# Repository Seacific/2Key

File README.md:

# 2Key
Simple 2 Key keypad designed for the rhythm game osu!

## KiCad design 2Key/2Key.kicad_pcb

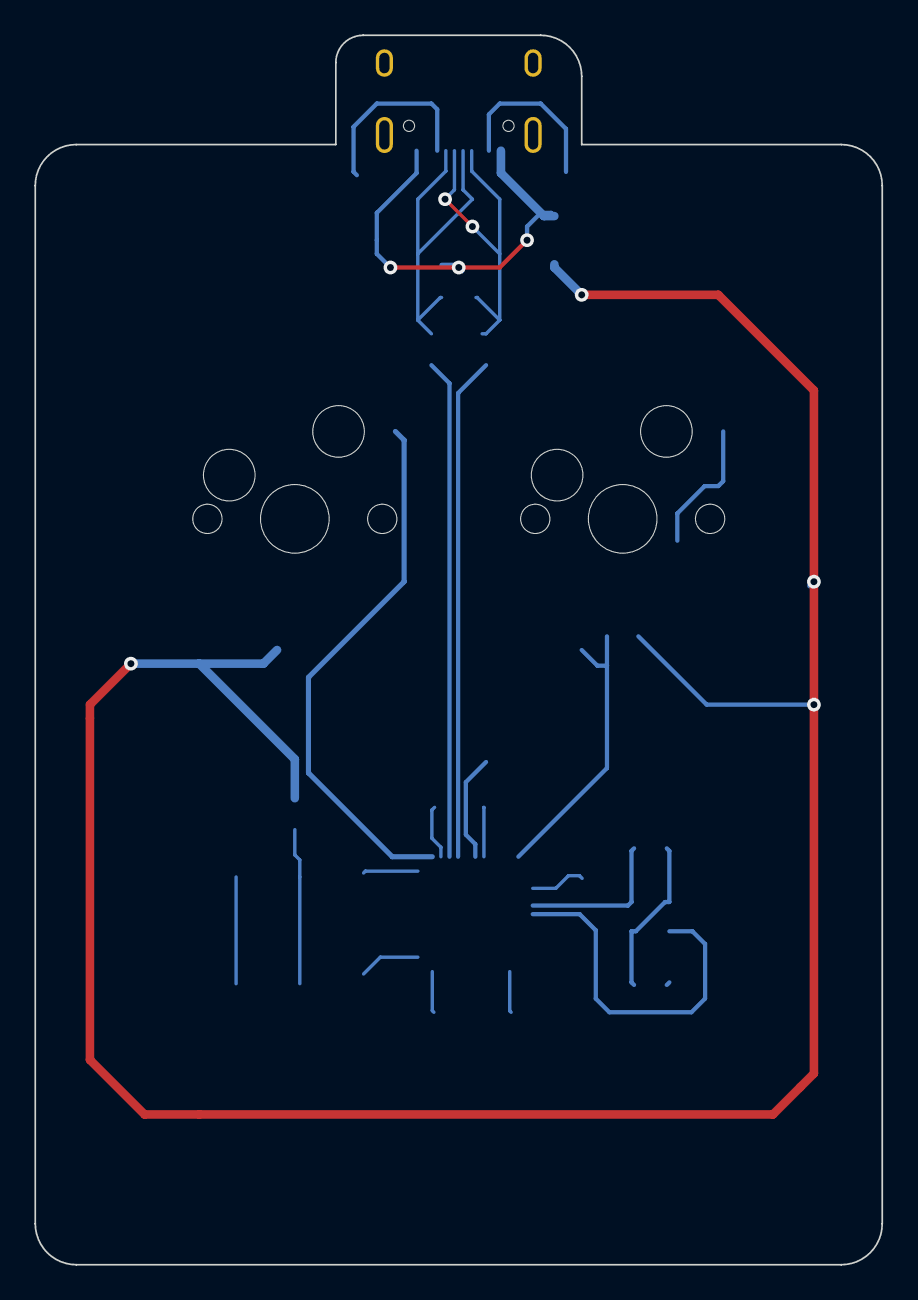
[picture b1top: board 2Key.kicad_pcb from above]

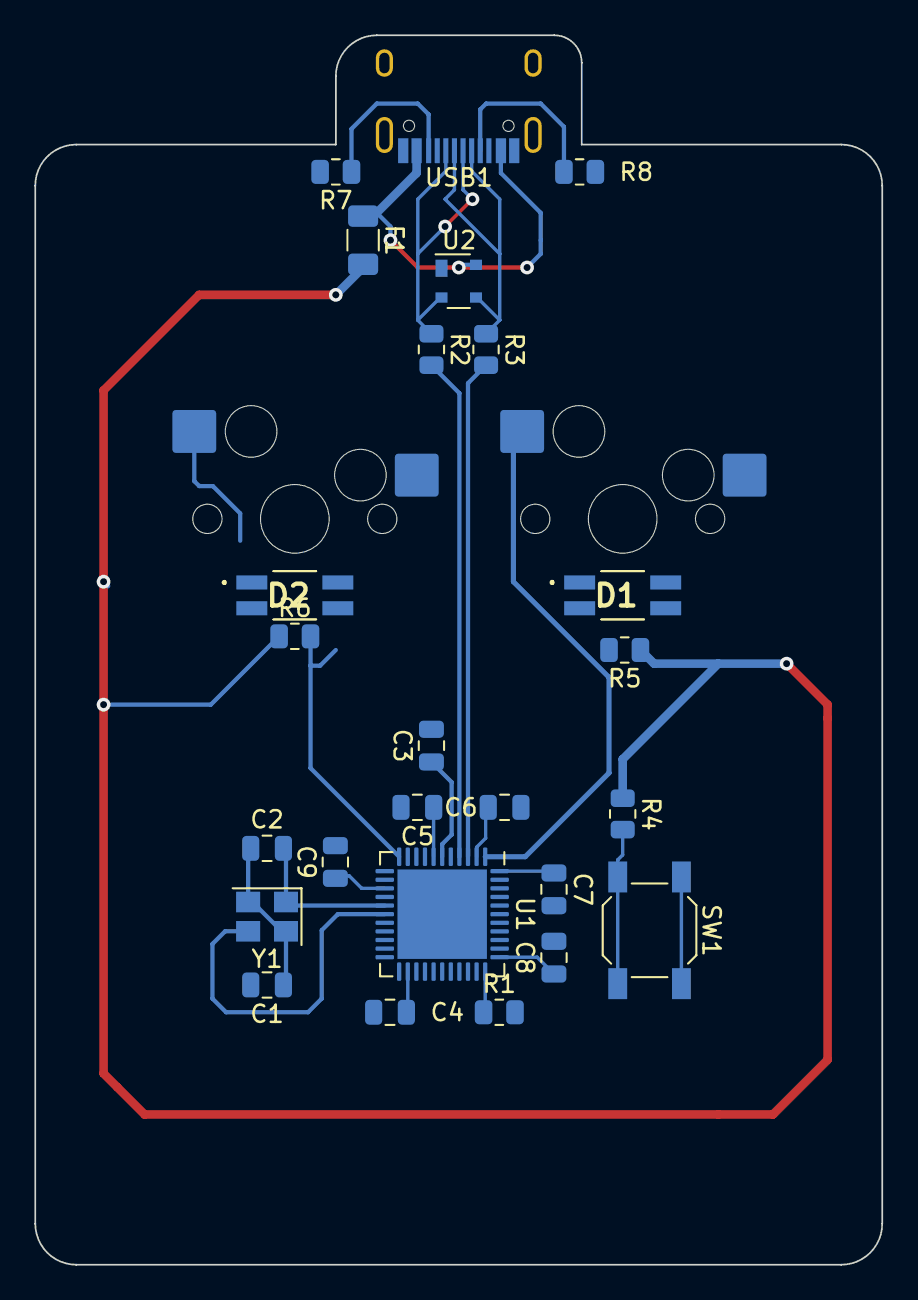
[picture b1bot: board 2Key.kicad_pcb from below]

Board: 2 copper layers, 49.2 x 71.4 mm, 27 parts (25 on the bottom side), 18 nets.

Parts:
C1, C2: 22pF; C_0805_2012Metric
C3: 1uF; C_0805_2012Metric
C4, C5, C6, C8, C9: 0.1uF; C_0805_2012Metric
C7: 10uF; C_0805_2012Metric
D1, D2: SK6812MINI; SK6812MINIE
F1: 500mA; Fuse_1206_3216Metric
MX1, MX2: MX-NoLED; MX-Hotswap-1U
R1, R4, R5, R6: 10k; R_0805_2012Metric
R2, R3: 22; R_0805_2012Metric
R7, R8: 5.1k; R_0805_2012Metric
SW1: SW_Push; SW_SPST_SKQG_WithStem
U1: ATmega32U4-M; QFN-44-1EP_7x7mm_P0.5mm_EP5.2x5.2mm
U2: PRTR5V0U2X; SOT-143
USB1: HRO-TYPE-C-31-M-12; HRO-TYPE-C-31-M-12-Assembly
Y1: 16MHz; Crystal_SMD_3225-4Pin_3.2x2.5mm

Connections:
+5V: C4.1, C5.1, C6.1, C7.1, C8.1, C9.1, D1.4 (VDD), D2.4 (VDD), F1.2, R4.1, R5.1, R6.1, U1.7 (VBUS)
D+: R2.1, U2.2 (IO1), USB1.6 (DP1), USB1.8 (DP2)
D-: R3.1, U2.3 (IO2), USB1.5 (DN2), USB1.7 (DN1)
GND: C1.1, C2.1, C3.2, C4.2, C5.2, C6.2, C7.2, C8.2, C9.2, D1.2 (VSS), D2.2 (VSS), MX1.1 (COL), MX2.1 (COL), R1.2, R7.2, R8.2, SW1.1, U1.5 (UGND), U1.15 (GND), U1.23 (GND), U1.35 (GND), U1.43 (GND), U1.45 (GND), U2.1 (GND), USB1.1 (GND), USB1.12 (GND), USB1.13 (SHIELD), Y1.2, Y1.4
unnamed: C1.2, U1.17 (XTAL1), Y1.3
unnamed: C2.2, U1.16 (XTAL2), Y1.1
unnamed: C3.1, U1.6 (UCAP)
unnamed: D1.1 (DOUT), D2.3 (DIN)
unnamed: MX1.2 (ROW), R5.2, U1.11 (PB3)
unnamed: MX2.2 (ROW), R6.2, U1.1 (PE6)
unnamed: R1.1, U1.33 (~HWB/PE2)
unnamed: R2.2, U1.4 (D+)
unnamed: R3.2, U1.3 (D-)
unnamed: R4.2, SW1.2, U1.13 (~RESET)
unnamed: R7.1, USB1.10 (CC2)
unnamed: R8.1, USB1.4 (CC1)
RGBLED: D1.3 (DIN), U1.26 (PD6)
VCC: F1.1, U1.2 (UVCC), U1.14 (VCC), U1.24 (AVCC), U1.34 (VCC), U1.44 (AVCC), U2.4 (VCC), USB1.2 (VBUS), USB1.11 (VBUS)

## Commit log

2022-12-01 Finished Schematic
2022-12-02 Started PCB
2022-12-03 Save Progress
2022-12-03 Added Submodule
2022-12-03 README
2022-12-03 Added PCB Image
2022-12-03 Updated PCB
2022-12-04 Remade PCB with the MU Chip
    Remade the PCB with the MU Chip and switched to reverse mounted LEDs
